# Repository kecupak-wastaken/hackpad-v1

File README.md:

# hackpad-v1
First time using any type of cad. 

This hackpad serves mostly as media control.

# case

# shcematic

# PCB

# BOM:

5x SK6812 MINI Leds

1x XIAO RP2040

4x Blank DSA Keycaps

4x Cherry MX Switches

4x M3x16 Bolt

4x M3 Heatset

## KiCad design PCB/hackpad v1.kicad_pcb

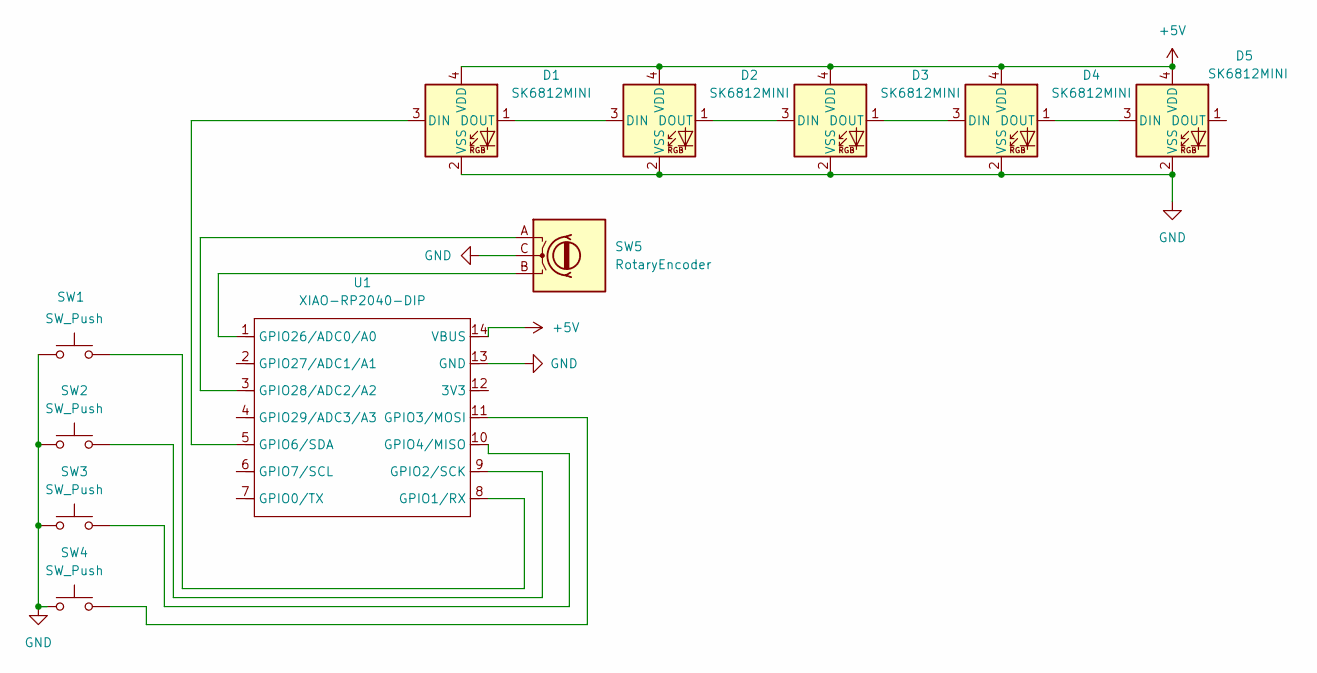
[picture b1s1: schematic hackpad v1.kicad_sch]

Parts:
D1, D2, D3, D4, D5: SK6812MINI; LED_SK6812MINI_PLCC4_3.5x3.5mm_P1.75mm
SW1, SW2, SW3, SW4: SW_Push; SW_Cherry_MX_1.00u_PCB
SW5: RotaryEncoder; RotaryEncoder_Alps_EC11E-Switch_Vertical_H20mm
U1: XIAO-RP2040-DIP; XIAO-RP2350-DIP

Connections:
+5V: D1.4 (VDD), D2.4 (VDD), D3.4 (VDD), D4.4 (VDD), D5.4 (VDD), U1.14 (VBUS)
GND: D1.2 (VSS), D2.2 (VSS), D3.2 (VSS), D4.2 (VSS), D5.2 (VSS), SW1.1, SW2.1, SW3.1, SW4.1, SW5.C, U1.13 (GND)
unnamed: D1.3 (DIN), U1.5 (GPIO6/SDA)
unnamed: D1.1 (DOUT), D2.3 (DIN)
unnamed: D2.1 (DOUT), D3.3 (DIN)
unnamed: D3.1 (DOUT), D4.3 (DIN)
unnamed: D4.1 (DOUT), D5.3 (DIN)
unnamed: SW1.2, U1.8 (GPIO1/RX)
unnamed: SW2.2, U1.9 (GPIO2/SCK)
unnamed: SW4.2, U1.11 (GPIO3/MOSI)
unnamed: SW3.2, U1.10 (GPIO4/MISO)
unnamed: SW5.B, U1.1 (GPIO26/ADC0/A0)
unnamed: SW5.A, U1.3 (GPIO28/ADC2/A2)

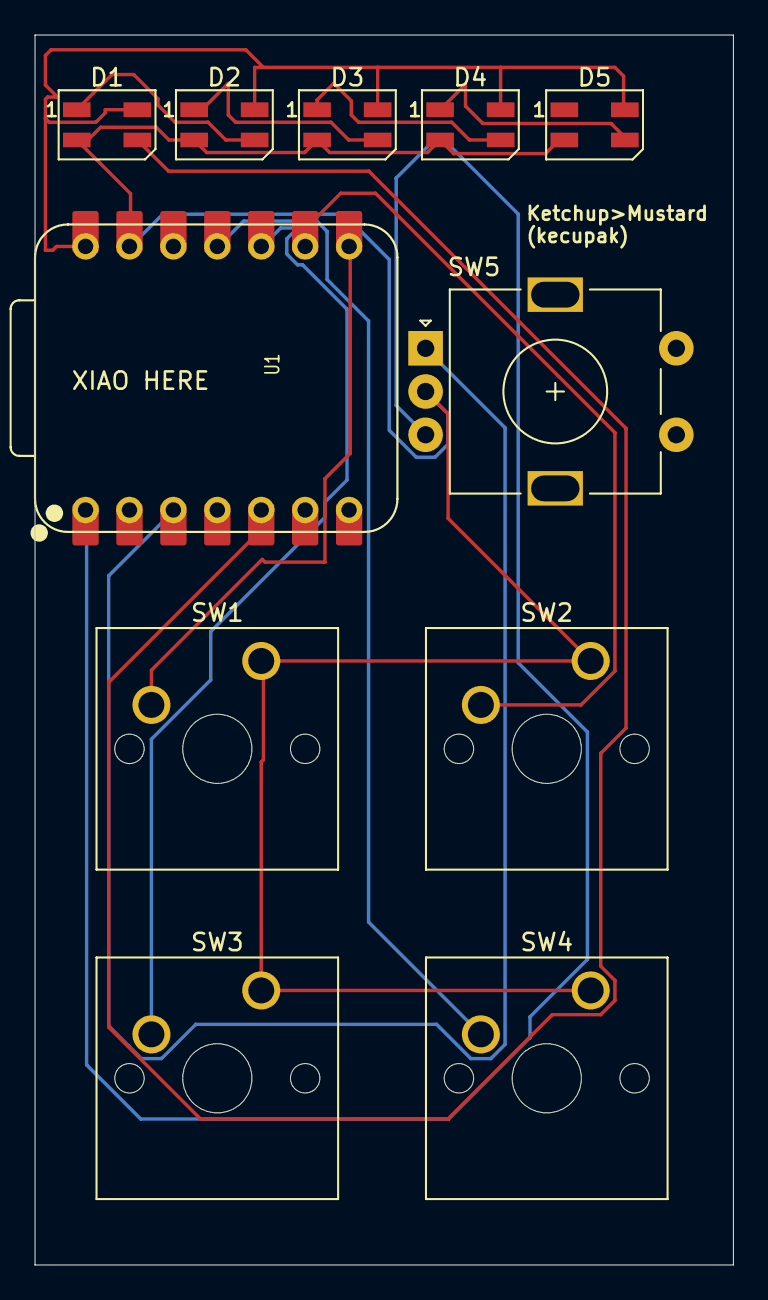
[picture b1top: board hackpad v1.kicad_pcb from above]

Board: 2 copper layers, 40.4 x 71.1 mm, 11 parts (0 on the bottom side), 13 nets.

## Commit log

2025-12-15 main.py
2025-12-16 README.md
